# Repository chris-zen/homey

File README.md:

# My Smart Home

This is my second round on building devices for my Smart Home (see [this other project](https://github.com/chris-zen/energy-monitoring) for my first attempt to build an energy monitoring system).

I am currently planning to build the following controllers:
- [Blinds controller](blinds): To bring up and down the blinds remotely.
- [Portable sensors](portable-sensors): To measure internal and external sensors (such as temperature and humidity), and provide a portable user interface.
- [Heater controller](heater): To switch on/off my heater according to the desired temperature, the current internal and external temperature and humidity, and other parameters.
- [Bathroom extractor controller](air-extractor): To control the bathroom air extractor according to presence, the humidity and time restrictions.

This time I will use [ESP8266](https://www.espressif.com/en/products/hardware/esp8266ex/overview) and [Mongoose-OS](https://mongoose-os.com/) as the base for the controllers.

I was planning to have a similar setup for my [base station](base-station) as for my previous project (see [this](https://github.com/chris-zen/energy-monitoring/wiki/Base-station) for further information), but my mind changed immediately as soon as I discovered the amazing [Project of Things](https://iot.mozilla.org/) from Mozilla. So my next challenge will be to figure out how to integrate my devices into the gateway (which I already have running in my Raspberry Pi, and fully working with my other [Z-Wave](http://www.z-wave.com/learn) devices).

# Media

- [Building my blinds controller](https://photos.app.goo.gl/Czdh2BhWPQBsjujQ9)
- [How I failed to build my first blinds controller](https://aloneinthehack.wordpress.com/2018/08/08/how-did-i-fail-to-build-my-first-blinds-controller/)

# Notes

- I followed [this guide](https://jnavila.github.io/plotkicadsch/) to make Kicad projects fit nicer with git

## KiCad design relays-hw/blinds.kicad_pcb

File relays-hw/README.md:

# Relays hardware

This project contains the hardware design for the controllers using relays.

All [libraries](libraries), [footprints](footprints) and [3D models](packages3d) (a part from the standard ones comming with Kicad) have been included in the project to avoid missing dependencies in the future.

I also include [plots](plots) for the board in case you just want to start building one without having to deal with Kicad.

# Attributions

- ESP8266 Kicad designs from [here](https://github.com/jdunmire/kicad-ESP8266)
- RELAY_PE Kicad designs from [here](http://smisioto.no-ip.org/elettronica/kicad/kicad-en.htm)

# License

This work is licensed under a [Creative Commons Attribution 4.0 International License](http://creativecommons.org/licenses/by/4.0/).

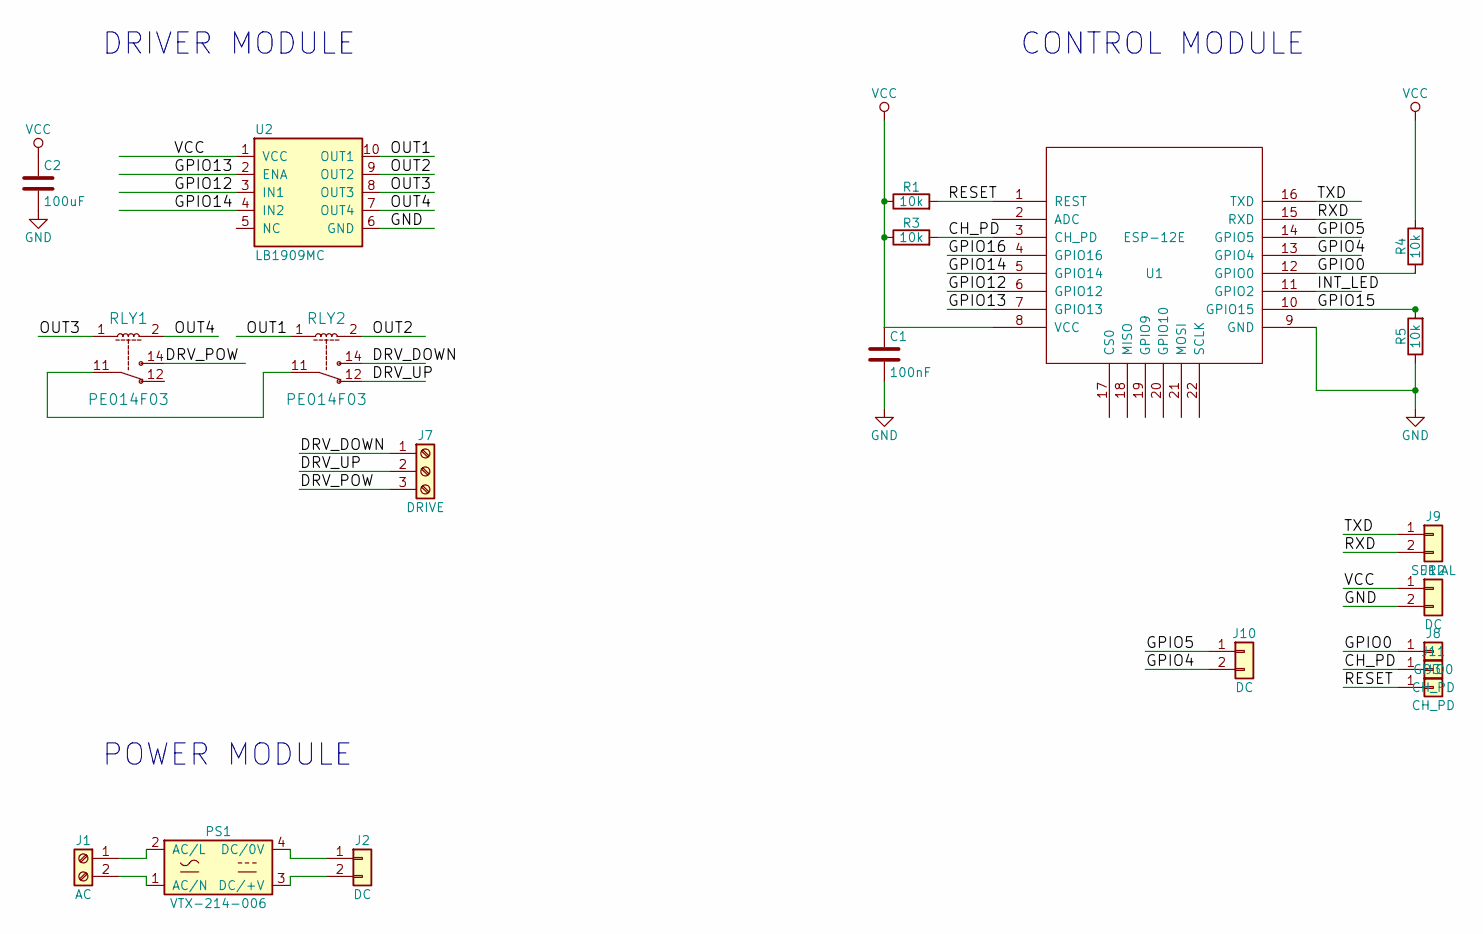
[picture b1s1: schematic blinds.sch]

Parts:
C1: 100nF; C_0805_HandSoldering
C2: 100uF; C_0805_HandSoldering
J1: AC; TerminalBlock_Pheonix_MKDS1.5-2pol
J2, J10, J12: DC; Pin_Header_Straight_1x02_Pitch2.54mm
J3, J11: CH_PD; Pin_Header_Straight_1x01_Pitch2.54mm
J7: DRIVE; TerminalBlock_Pheonix_MKDS1.5-3pol
J8: GPIO0; Pin_Header_Straight_1x01_Pitch2.54mm
J9: SERIAL; Pin_Header_Straight_1x02_Pitch2.54mm
PS1: VTX-214-006
R1, R3, R4, R5: 10k; R_0805_HandSoldering
RLY1, RLY2: PE014F03; relay_PE
U1: ESP-12E; ESP-12E_SMD
U2: LB1909MC

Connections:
/CH_PD: J11.1, R3.2, U1.3 (CH_PD)
/DRV_DOWN: J7.1, RLY2.14
/DRV_POW: J7.3, RLY1.14
/DRV_UP: J7.2, RLY2.12
/GPIO0: J8.1, R4.1, U1.12 (GPIO0)
/GPIO4: J10.2, U1.13 (GPIO4)
/GPIO5: J10.1, U1.14 (GPIO5)
/GPIO12: U1.6 (GPIO12), U2.3 (IN1)
/GPIO13: U1.7 (GPIO13), U2.2 (ENA)
/GPIO14: U1.5 (GPIO14), U2.4 (IN2)
/GPIO15: R5.2, U1.10 (GPIO15)
/GPIO16: U1.4 (GPIO16)
/INT_LED: U1.11 (GPIO2)
/OUT1: RLY2.1, U2.10 (OUT1)
/OUT2: RLY2.2, U2.9 (OUT2)
/OUT3: RLY1.1, U2.8 (OUT3)
/OUT4: RLY1.2, U2.7 (OUT4)
/RESET: J3.1, R1.2, U1.1 (REST)
/RXD: J9.2, U1.15 (RXD)
/TXD: J9.1, U1.16 (TXD)
GND: C1.2, C2.2, J12.2, R5.1, U1.9 (GND), U2.6 (GND)
unnamed: J1.1, PS1.2 (AC/L)
unnamed: J1.2, PS1.1 (AC/N)
unnamed: J2.1, PS1.4 (DC/0V)
unnamed: J2.2, PS1.3 (DC/+V)
unnamed: RLY1.11, RLY2.11
VCC: C1.1, C2.1, J12.1, R1.1, R3.1, R4.2, U1.8 (VCC), U2.1 (VCC)

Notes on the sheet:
DRIVER MODULE
POWER MODULE
CONTROL MODULE

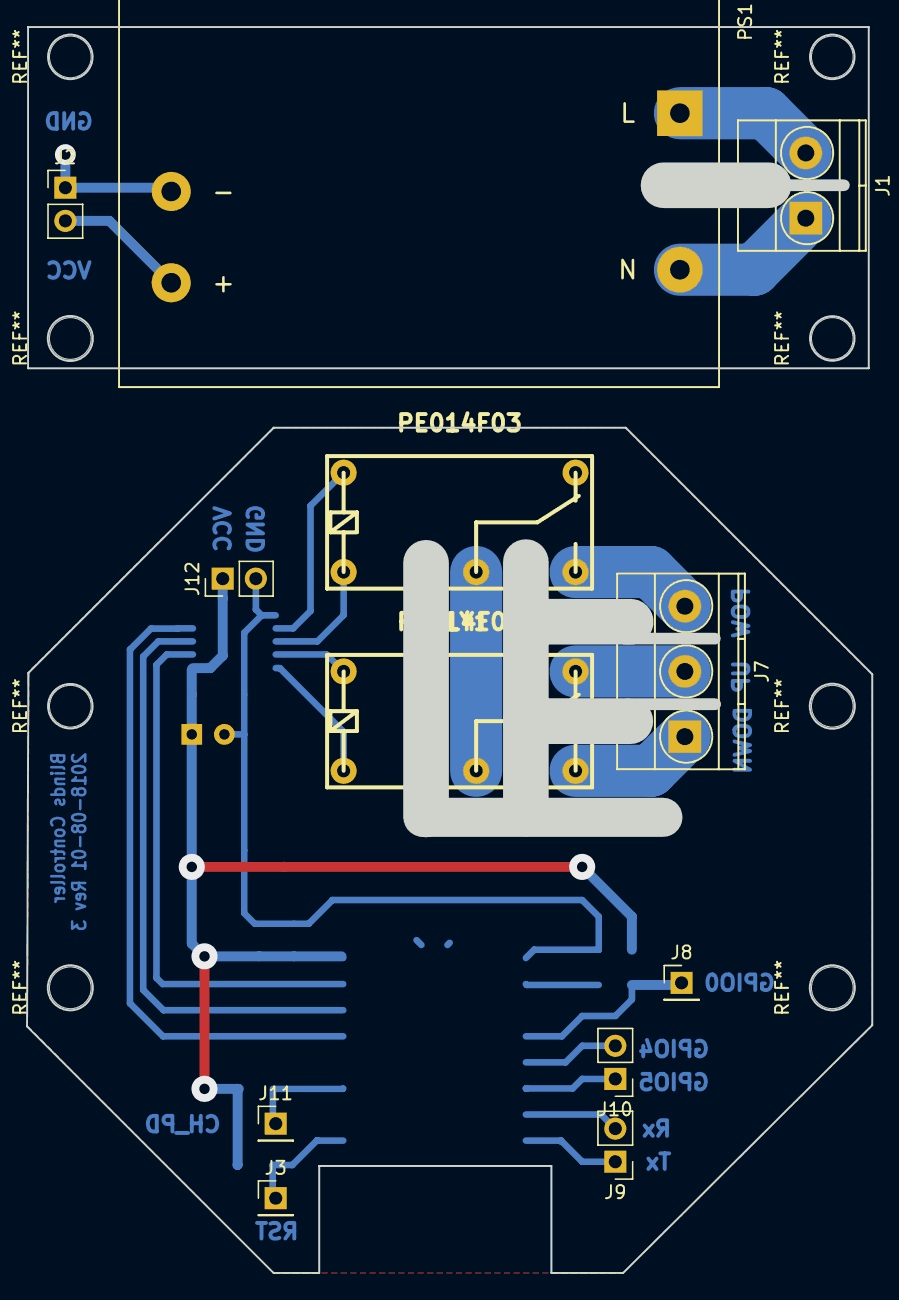
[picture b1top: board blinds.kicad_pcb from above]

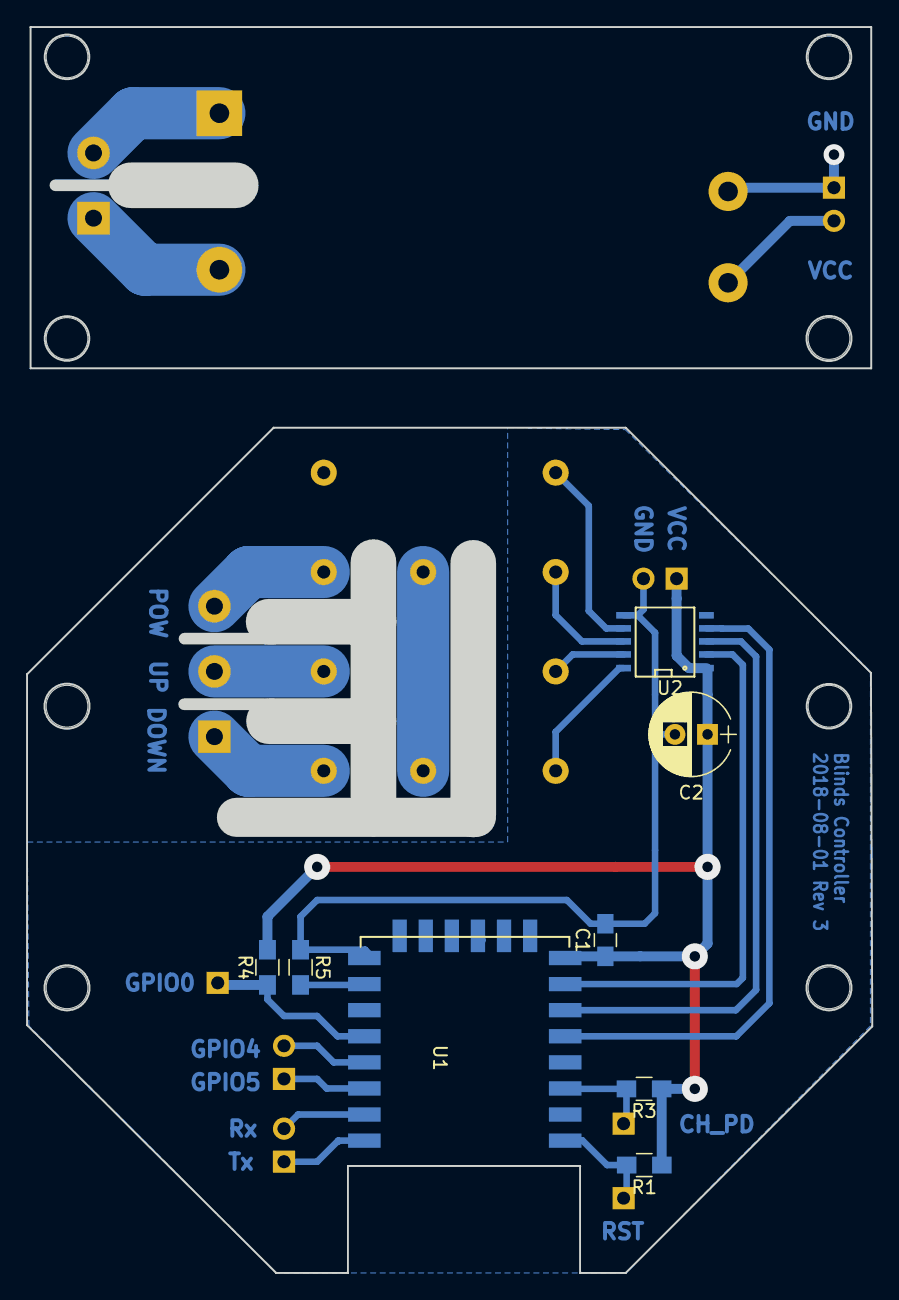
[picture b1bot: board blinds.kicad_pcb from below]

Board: 2 copper layers, 61.5 x 92.2 mm, 20 parts (8 on the bottom side), 25 nets.

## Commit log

2018-08-05 2nd revision for blinds
2018-08-05 Added initial README for the overall project
2018-08-05 Updated docs. Blinds power off when both up/down switches are on.
2018-08-05 Added link to ESP8266
2018-08-05 git setup for kicad
2018-08-06 Revision 3
2018-08-06 Updated docs with Project of Things
2018-08-07 Simplified RPC interface for blinds
2018-08-07 Prevent the direction relay from changing while the power is on
2018-08-07 Better handling of switch interrupts
2018-08-07 Reorganised RPC calls
2018-08-08 Updated main README
2018-08-09 Updated and added docs. Reorganised folders.
2018-08-09 Fixed docs
2018-08-09 Fixing docs
2018-08-09 Updated docs for TH sensor
2018-08-09 [blinds] fix rpc calls
2018-08-15 Initial firmware for the heater.
2018-08-15 TH firmware for the portable sensors.
2018-08-15 Added README for base-station
2018-08-15 Added notes for the base station
2018-08-15 Fix reference to portable sensors
2018-08-26 [portable-sensors] MQTT message only contains defined sensors.
2018-08-26 [base-station] Updated docs
2018-08-26 [heater] Removed thermostat logic & Added MQTT interface for heater control.
2018-08-26 Updated .gitignore files
2018-09-11 [base-station] Updated README with thermostat docker run
2018-09-11 [heater] Improved status reporting
2018-09-11 Added .DS_Store to .gitignore
2018-10-21 Added thermostat
2018-11-18 [heater] Fix: level undefined
